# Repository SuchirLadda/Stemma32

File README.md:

# Stemma32
Custom STM32 dev board with UART, I²C, USB, and SWD interfaces. Designed in KiCad for embedded prototyping.

## Overview
A custom-designed STM32 development board featuring UART, I²C, and USB communication interfaces, intended for embedded systems prototyping and peripheral interfacing. This board is built around the STM32F103C8T6 microcontroller and includes key components such as an external crystal oscillator, onboard boot configuration switch, SWD programming header, and power regulation circuitry.

Pin layout and peripheral configuration were assisted by STM32CubeIDE, which was used to validate the pin mappings and peripheral assignments during design.

## Features
- STM32F103C8T6 MCU
- USB-to-Serial (UART) communication
- UART and I²C breakout for peripherals
- SWD programming/debug interface
- Onboard 3.3V AMS1117 voltage regulator
- External 8 MHz crystal oscillator
- Boot configuration slide switch  
- KiCad 8 project files included

## Repository Contents
- `/kicad/` – Schematic and PCB layout
- `/images/` – 3D model and board render

### Front View – 3D PCB Render

### Rear View – 3D PCB Render

## 🤝 Sponsorship

This board was manufactured and assembled with the generous support of **[PCBWay](https://www.pcbway.com/)**.

The production quality and turnaround time were excellent. From fabrication to component assembly, everything arrived perfectly aligned and functional.

PCBWay’s engineering team responds quickly and is very understanding when it comes to resolving issues in the assembly process. I highly recommend them for custom PCB projects.

## Physical Board Photos

### Assembled Board – Front

### Assembled Board – Rear

### Power Indicator Test

### All Units Assembled

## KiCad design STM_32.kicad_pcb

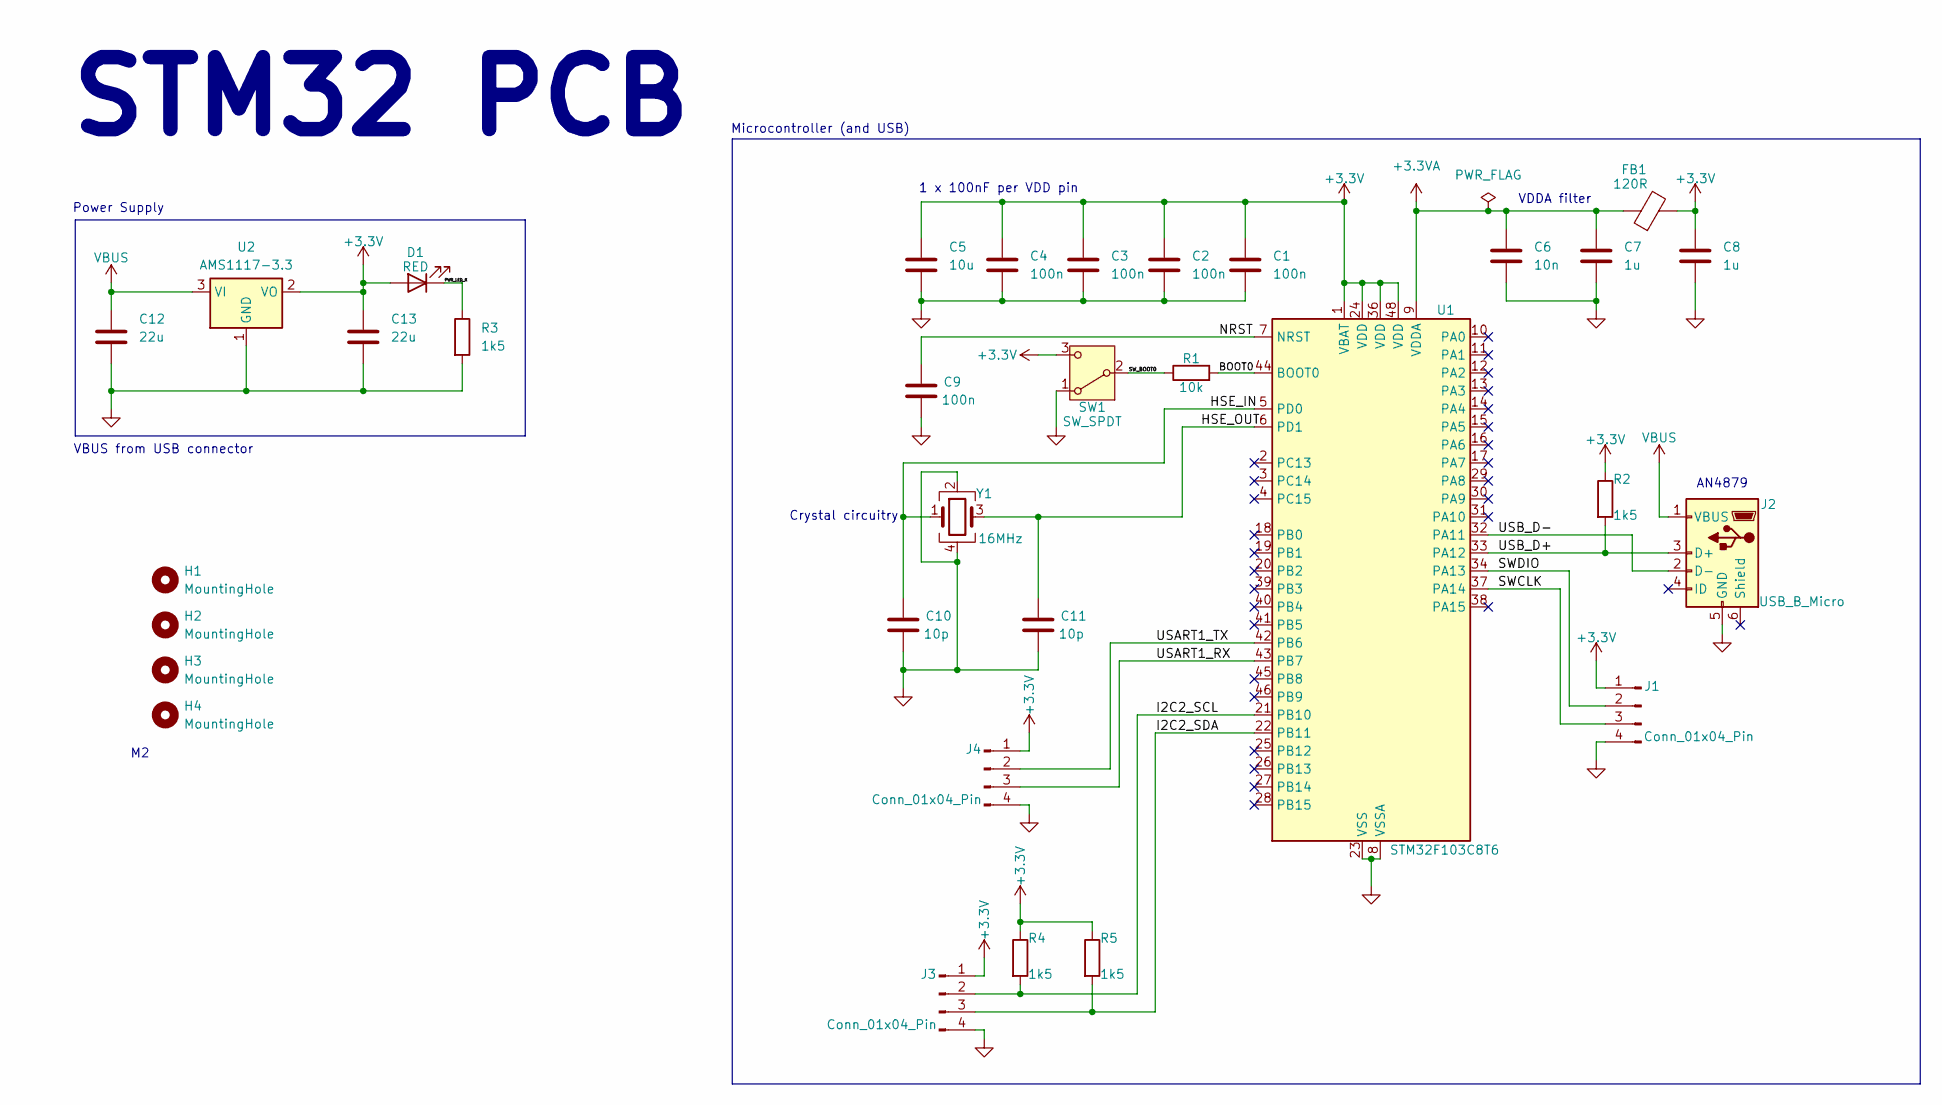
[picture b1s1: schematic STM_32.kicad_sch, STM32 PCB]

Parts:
C1, C2, C3, C4, C9: 100n; C_0402_1005Metric
C5: 10u; C_0603_1608Metric
C6: 10n; C_0402_1005Metric
C7, C8: 1u; C_0402_1005Metric
C10, C11: 10p; C_0402_1005Metric
C12, C13: 22u; C_0805_2012Metric
D1: RED; LED_0603_1608Metric
FB1: 120R; L_0603_1608Metric
H1, H2, H3, H4: MountingHole; MountingHole_2.2mm_M2
J1, J3, J4: Conn_01x04_Pin; PinHeader_1x04_P2.54mm_Vertical
J2: USB_B_Micro; USB_Micro-B_Wuerth_629105150521
R1: 10k; R_0402_1005Metric
R2, R3, R4, R5: 1k5; R_0402_1005Metric
SW1: SW_SPDT; SW_SPDT_PCM12
U1: STM32F103C8T6; LQFP-48_7x7mm_P0.5mm
U2: AMS1117-3.3; SOT-223-3_TabPin2
Y1: 16MHz; Crystal_SMD_3225-4Pin_3.2x2.5mm

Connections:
+3.3V: C1.1, C2.1, C3.1, C4.1, C5.1, C8.1, C13.1, D1.2 (A), FB1.2, J1.1, J3.1, J4.1, R2.1, R4.1, R5.1, SW1.3 (C), U1.1 (VBAT), U1.24 (VDD), U1.36 (VDD), U1.48 (VDD), U2.2 (VO)
+3.3VA: C6.1, C7.1, FB1.1, U1.9 (VDDA)
/BOOT0: R1.2, U1.44 (BOOT0)
/HSE_IN: C10.1, U1.5 (PD0), Y1.1
/HSE_OUT: C11.1, U1.6 (PD1), Y1.3
/I2C2_SCL: J3.2, R4.2, U1.21 (PB10)
/I2C2_SDA: J3.3, R5.2, U1.22 (PB11)
/NRST: C9.1, U1.7 (NRST)
/PWR_LED_K: D1.1 (K), R3.1
/SWCLK: J1.3, U1.37 (PA14)
/SWDIO: J1.2, U1.34 (PA13)
/SW_BOOT0: R1.1, SW1.2 (B)
/USART1_RX: J4.3, U1.43 (PB7)
/USART1_TX: J4.2, U1.42 (PB6)
/USB_D+: J2.3 (D+), R2.2, U1.33 (PA12)
/USB_D-: J2.2 (D-), U1.32 (PA11)
GND: C1.2, C2.2, C3.2, C4.2, C5.2, C6.2, C7.2, C8.2, C9.2, C10.2, C11.2, C12.2, C13.2, J1.4, J2.5 (GND), J3.4, J4.4, R3.2, SW1.1 (A), U1.8 (VSSA), U1.23 (VSS), U1.35 (VSS), U1.47 (VSS), U2.1 (GND), Y1.2, Y1.4
VBUS: C12.1, J2.1 (VBUS), U2.3 (VI)

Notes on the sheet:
Crystal circuitry
STM32 PCB
AN4879
VDDA filter
Microcontroller (and USB)
1 x 100nF per VDD pin
Power Supply
VBUS from USB connector

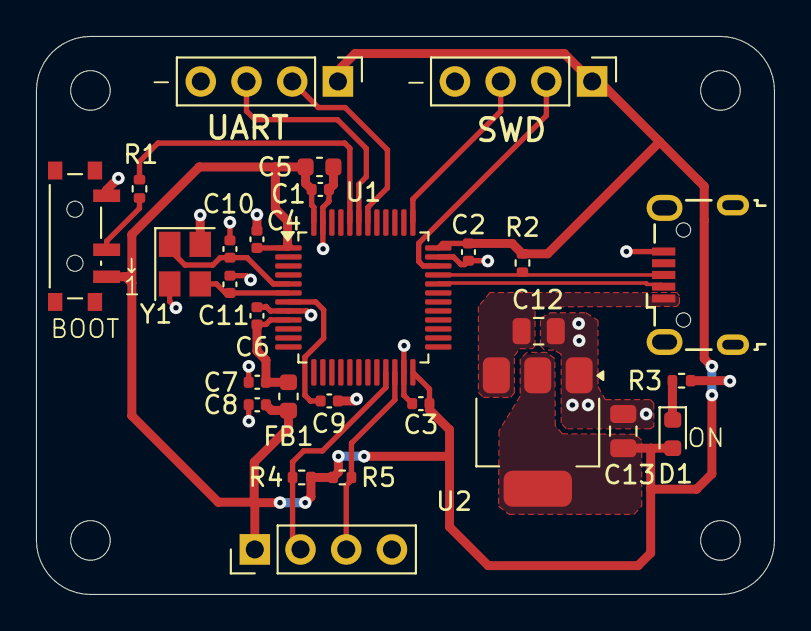
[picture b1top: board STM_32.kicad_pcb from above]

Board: 2 copper layers, 41.0 x 31.0 mm, 32 parts (0 on the bottom side), 18 nets.

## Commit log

2025-05-22 added project files
2025-05-22 Create placeholder
2025-05-22 added images
